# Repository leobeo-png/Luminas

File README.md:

# Luminas
Rhythm game controller development (Pro Micro). WIP <br>
[Video Demo](https://www.youtube.com/watch?v=vNHZUSEBsMY "Early Prototype")
[Video Demo](https://www.youtube.com/watch?v=JDYHQ-9xTno "Prototype Update")
---
## Description
 - Custom keyboard NKRO HID 
 - PCB size for 15.6" laptop
 - ToF sensors instead of IR for compactness
---
## Components Used:
 - Arduino Pro Micro
 - MPR121 Modules x3
 - VL53L0X ToF sensors x2 
 - TCA9548 I2C Multiplexer
 - Pull-up resistors
---
## Goals
 - Improve the design of the PCB 
 - Reaserch and design the casing
--- 
## What I Learnt so Far 
 - HID (descriptors, how NKRO works)
 - PCB schematic designing
 - Diving further into I2C

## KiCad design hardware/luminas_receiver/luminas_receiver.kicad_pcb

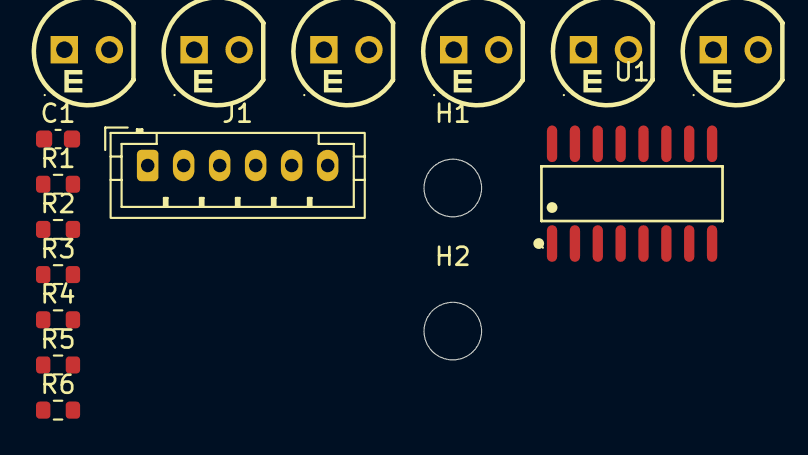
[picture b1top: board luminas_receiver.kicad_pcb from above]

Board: 2 copper layers, 17 parts (0 on the bottom side), 12 nets, no tracks yet.

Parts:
C1: 100nF; C_0603_1608Metric
H1, H2: MountingHole; MountingHole_3.2mm_M3
J1: Conn_01x06; JST_PH_B6B-PH-K_1x06_P2.00mm_Vertical
Q1, Q2, Q3, Q4, Q5, Q6: PT333-3B_C5134; SENSOR-TH_PT333-3B
R1, R2, R3, R4, R5, R6: 47k; R_0603_1608Metric
U1: 74LV4051D,118; SO-16_L9.9-W3.9-P1.27-LS6.0-BL

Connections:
+3V3: C1.1, J1.1, Q1.2 (C), Q2.2 (C), Q3.2 (C), Q4.2 (C), Q5.2 (C), Q6.2 (C), U1.16 (VCC)
/Y0: Q1.1 (E), R1.1, U1.13 (Y0)
/Y1: Q2.1 (E), R2.1, U1.14 (Y1)
/Y2: Q3.1 (E), R3.1, U1.15 (Y2)
/Y3: Q4.1 (E), R4.1, U1.12 (Y3)
/Y4: Q5.1 (E), R5.1, U1.1 (Y4)
/Y5: Q6.1 (E), R6.1, U1.5 (Y5)
AIR_OUT: J1.6, U1.3 (Z)
GND: C1.2, J1.2, R1.2, R2.2, R3.2, R4.2, R5.2, R6.2, U1.2 (Y6), U1.4 (Y7), U1.6 (~E), U1.7 (VEE), U1.8 (VSS)
IR_SEL0: J1.3, U1.11 (S0)
IR_SEL1: J1.4, U1.10 (S1)
IR_SEL2: J1.5, U1.9 (S2)

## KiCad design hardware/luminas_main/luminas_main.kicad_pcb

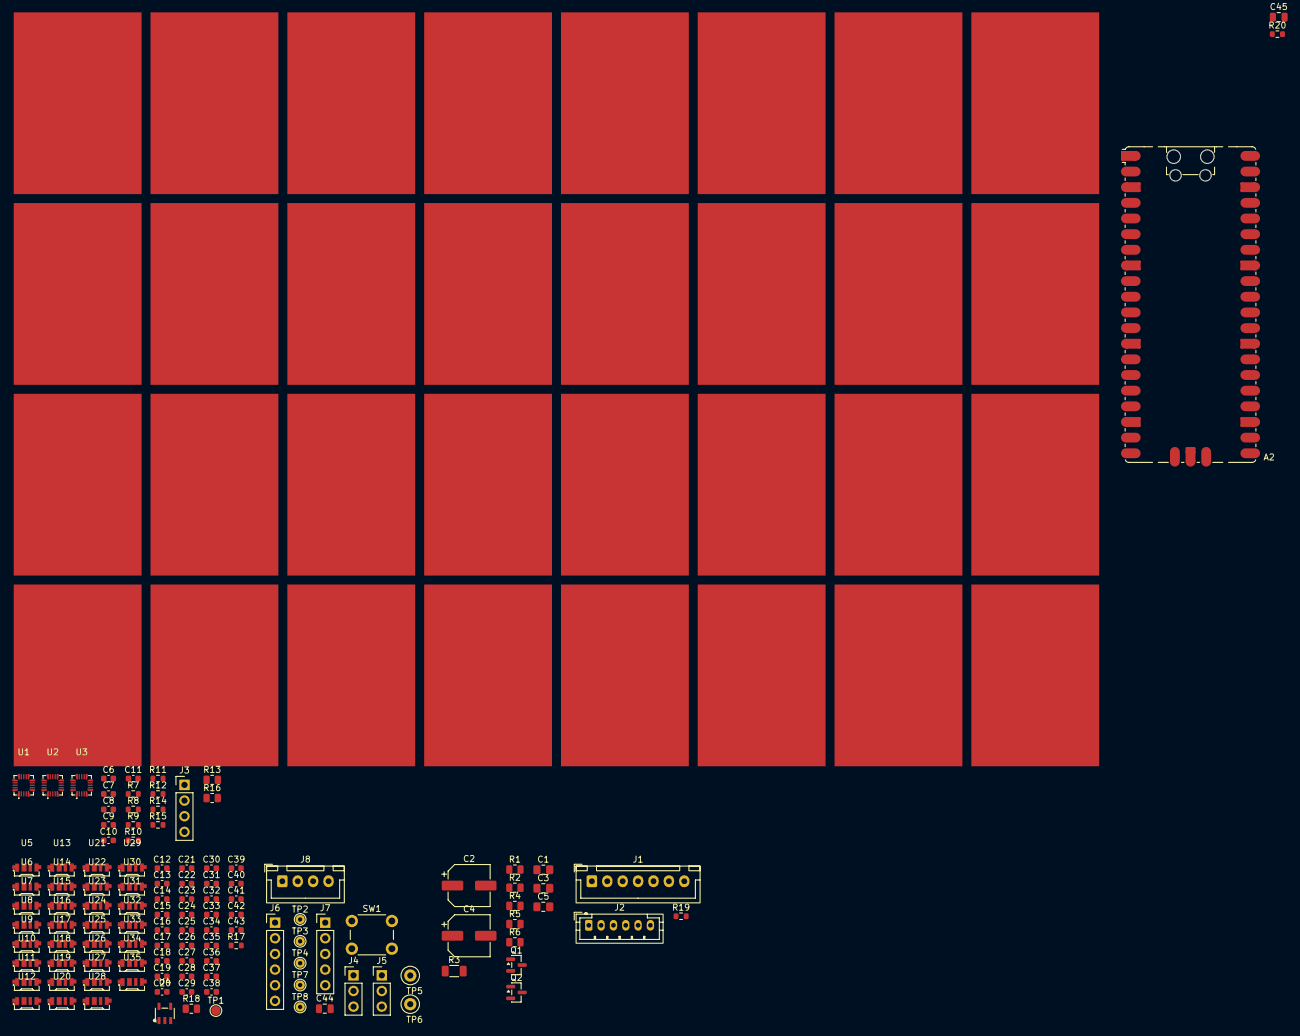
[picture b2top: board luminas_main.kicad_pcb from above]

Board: 2 copper layers, 152 parts (0 on the bottom side), 107 nets, no tracks yet.

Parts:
A2: RaspberryPi_Pico; RaspberryPi_Pico_SMD_HandSolder
C1: 47nF; C_0805_2012Metric_Pad1.18x1.45mm_HandSolder
C2: 100uF 16V; CP_Elec_6.3x7.7
C3: 10uF; C_0805_2012Metric_Pad1.18x1.45mm_HandSolder
C4: 100uF; CP_Elec_6.3x7.7
C5: 10nF; C_0805_2012Metric_Pad1.18x1.45mm_HandSolder
C6, C7, C8, C9, C10, C11, C12, C13, C14, C15, C16, C17, C18, C19, C20, C21, C22, C23, C24, C25, C26, C27, C28, C29, C30, C31, C32, C33, C34, C35, C36, C37, C38, C39, C40, C41, C42, C43: 100nF; C_0603_1608Metric
C44: 100nF; C_0805_2012Metric
C45: 1nF; C_0805_2012Metric
E1, E2, E3, E4, E5, E6, E7, E8, E9, E10, E11, E12, E13, E14, E15, E16, E17, E18, E19, E20, E21, E22, E23, E24, E25, E26, E27, E28, E29, E30, E31, E32: Touch_Pad
J1: IR conn; JST_XH_B7B-XH-A_1x07_P2.50mm_Vertical
J2: Air out conn; JST_PH_B6B-PH-K_1x06_P2.00mm_Vertical
J3: Spare I2C1; PinHeader_1x04_P2.54mm_Vertical
J4: SWD header; PinHeader_1x03_P2.54mm_Vertical
J5: UART header; PinHeader_1x03_P2.54mm_Vertical
J6: Logic-analyser header; PinHeader_1x06_P2.54mm_Vertical
J7: Spare Analog; PinHeader_1x05_P2.54mm_Vertical
J8: Conn_01x04; JST_XH_B4B-XH-A_1x04_P2.50mm_Vertical
Q1: AO3401A; SOT-23
Q2: 2N7002; SOT-23
R1, R4, R5, R6: 100kΩ; R_0805_2012Metric
R2: 47kΩ; R_0805_2012Metric
R3: 0Ω; R_1206_3216Metric
R7, R8: 2.2kΩ; R_0603_1608Metric
R9, R14, R15: 10kΩ; R_0603_1608Metric
R10, R11, R12: 75kΩ 1%; R_0603_1608Metric
R13, R16: 2.2kΩ; R_0805_2012Metric
R17: 33Ω; R_0603_1608Metric
R18: 0Ω; R_0805_2012Metric
R19: 100k; R_0603_1608Metric
R20: 0Ω; R_0603_1608Metric
SW1: RESET; SW_PUSH_6mm
TP1: LED_CHAIN_END; TestPoint_Pad_D1.5mm
TP2: +3V3; TestPoint_THTPad_D1.5mm_Drill0.7mm
TP3: 5V_SW; TestPoint_THTPad_D1.5mm_Drill0.7mm
TP4: VBUS; TestPoint_THTPad_D1.5mm_Drill0.7mm
TP5, TP6: GND; TestPoint_Loop_D2.50mm_Drill1.0mm
TP7: AIR_OUT; TestPoint_THTPad_D1.5mm_Drill0.7mm
TP8: IR_EN; TestPoint_THTPad_D1.5mm_Drill0.7mm
U1, U2, U3: MPR121QR2; QFN-20_L3.0-W3.0-P0.40-BL
U4: 74AHCT1G125GV; SOT-23-5_L3.0-W1.7-P0.95-LS2.8-BL
U5, U6, U7, U8, U9, U10, U11, U12, U13, U14, U15, U16, U17, U18, U19, U20, U21, U22, U23, U24, U25, U26, U27, U28, U29, U30, U31, U32, U33, U34, U35: WS2812B-4020-V6; LED-SMD_4P-L4.0-W1.6-L

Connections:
5V_SW: C1.1, C2.1, C3.2, C4.1, C12.1, C13.1, C14.1, C15.1, C16.1, C17.1, C18.1, C19.1, C20.1, C21.1, C22.1, C23.1, C24.1, C25.1, C26.1, C27.1, C28.1, C29.1, C30.1, C31.1, C32.1, C33.1, C34.1, C35.1, C36.1, C37.1, C38.1, C39.1, C40.1, C41.1, C42.1, C43.1, J1.1, Q1.3 (D), R3.1, R5.1, TP3.1 (1_1), U4.5 (VCC), U5.2 (VDD), U6.2 (VDD), U7.2 (VDD), U8.2 (VDD), U9.2 (VDD), U10.2 (VDD), U11.2 (VDD), U12.2 (VDD), U13.2 (VDD), U14.2 (VDD), U15.2 (VDD), U16.2 (VDD), U17.2 (VDD), U18.2 (VDD), U19.2 (VDD), U20.2 (VDD), U21.2 (VDD), U22.2 (VDD), U23.2 (VDD), U24.2 (VDD), U25.2 (VDD), U26.2 (VDD), U27.2 (VDD), U28.2 (VDD), U29.2 (VDD), U30.2 (VDD), U31.2 (VDD), U32.2 (VDD), U33.2 (VDD), U34.2 (VDD), U35.2 (VDD)
+3V3: A2.36 (3V3), C6.1, C9.1, C11.1, J1.3, J2.1, J3.2, J7.5, R7.1, R8.1, R9.1, R13.2, R14.1, R15.1, R16.2, TP2.1 (1_1), U1.20 (VDD), U2.4 (ADDR), U2.20 (VDD), U3.20 (VDD)
/Touch/ZONE00: E1.1, U1.8 (ELE0)
/Touch/ZONE01: E2.1, U1.9 (ELE1)
/Touch/ZONE02: E3.1, U1.10 (ELE2)
/Touch/ZONE03: E4.1, U1.11 (ELE3)
/Touch/ZONE04: E5.1, U1.12 (ELE4)
/Touch/ZONE05: E6.1, U1.13 (ELE5)
/Touch/ZONE06: E7.1, U1.14 (ELE6)
/Touch/ZONE07: E8.1, U1.15 (ELE7)
/Touch/ZONE08: E9.1, U1.16 (ELE8)
/Touch/ZONE09: E10.1, U1.17 (ELE9)
/Touch/ZONE10: E11.1, U1.18 (ELE10)
/Touch/ZONE11: E12.1, U1.19 (ELE11)
/Touch/ZONE12: E13.1, U2.8 (ELE0)
/Touch/ZONE13: E14.1, U2.9 (ELE1)
/Touch/ZONE14: E15.1, U2.10 (ELE2)
/Touch/ZONE15: E16.1, U2.11 (ELE3)
/Touch/ZONE16: E17.1, U2.12 (ELE4)
/Touch/ZONE17: E18.1, U2.13 (ELE5)
/Touch/ZONE18: E19.1, U2.14 (ELE6)
/Touch/ZONE19: E20.1, U2.15 (ELE7)
/Touch/ZONE20: E21.1, U2.16 (ELE8)
/Touch/ZONE21: E22.1, U2.17 (ELE9)
/Touch/ZONE22: E23.1, U2.18 (ELE10)
/Touch/ZONE23: E24.1, U2.19 (ELE11)
/Touch/ZONE24: E25.1, U3.8 (ELE0)
/Touch/ZONE25: E26.1, U3.9 (ELE1)
/Touch/ZONE26: E27.1, U3.10 (ELE2)
/Touch/ZONE27: E28.1, U3.11 (ELE3)
/Touch/ZONE28: E29.1, U3.12 (ELE4)
/Touch/ZONE29: E30.1, U3.13 (ELE5)
/Touch/ZONE30: E31.1, U3.14 (ELE6)
/Touch/ZONE31: E32.1, U3.15 (ELE7)
AIR_OUT: C45.1, J2.6, R20.2, TP7.1 (1_1)
DBG0: A2.25 (GPIO19), J6.4
DBG1: A2.26 (GPIO20), J6.5
DBG2: A2.27 (GPIO21), J6.6
GND: A2.3 (GND), A2.8 (GND), A2.13 (GND), A2.18 (GND), A2.23 (GND), A2.28 (GND), A2.33 (AGND), A2.38 (GND), A2.D2 (GND), C2.2, C3.1, C4.2, C5.1, C6.2, C7.2, C8.2, C9.2, C10.2, C11.2, C12.2, C13.2, C14.2, C15.2, C16.2, C17.2, C18.2, C19.2, C20.2, C21.2, C22.2, C23.2, C24.2, C25.2, C26.2, C27.2, C28.2, C29.2, C30.2, C31.2, C32.2, C33.2, C34.2, C35.2, C36.2, C37.2, C38.2, C39.2, C40.2, C41.2, C42.2, C43.2, C44.2, C45.2, J1.2, J2.2, J3.1, J4.2, J5.1, J6.1, J7.1, J8.1, Q2.2 (S), R4.1, R6.2, R10.2, R11.2, R12.2, R19.2, SW1.2, TP5.1 (1_1), TP6.1 (1_1), U1.4 (ADDR), U1.6 (VSS), U2.6 (VSS), U3.6 (VSS), U4.1 (~OE), U4.3 (GND), U5.4 (VSS), U6.4 (VSS), U7.4 (VSS), U8.4 (VSS), U9.4 (VSS), U10.4 (VSS), U11.4 (VSS), U12.4 (VSS), U13.4 (VSS), U14.4 (VSS), U15.4 (VSS), U16.4 (VSS), U17.4 (VSS), U18.4 (VSS), U19.4 (VSS), U20.4 (VSS), U21.4 (VSS), U22.4 (VSS), U23.4 (VSS), U24.4 (VSS), U25.4 (VSS), U26.4 (VSS), U27.4 (VSS), U28.4 (VSS), U29.4 (VSS), U30.4 (VSS), U31.4 (VSS), U32.4 (VSS), U33.4 (VSS), U34.4 (VSS), U35.4 (VSS)
I2C0_SCL: A2.7 (GPIO5), J6.3, R8.2, U1.2 (SCL), U2.2 (SCL), U3.2 (SCL)
I2C0_SDA: A2.6 (GPIO4), J6.2, R7.2, U1.3 (SDA), U2.3 (SDA), U3.3 (SDA), U3.4 (ADDR)
I2C1_SCL: A2.5 (GPIO3), J3.4, R16.1
I2C1_SDA: A2.4 (GPIO2), J3.3, R13.1
IR_EN: A2.17 (GPIO13), J1.7, R19.1, TP8.1 (1_1)
IR_SEL0: A2.14 (GPIO10), J1.4, J2.3
IR_SEL1: A2.15 (GPIO11), J1.5, J2.4
IR_SEL2: A2.16 (GPIO12), J1.6, J2.5
LED_5V_EN: A2.19 (GPIO14), Q2.1 (G), R4.2
LED_DATA: A2.20 (GPIO15), R18.2, U4.2 (A)
unnamed: A2.31 (GPIO26_ADC0), R20.1
unnamed: C1.2, Q1.1 (G), R1.1, R2.2
unnamed: Q2.3 (D), R2.1
unnamed: R10.1, U1.7 (REXT)
unnamed: C7.1, U1.5 (VREG)
unnamed: R11.1, U2.7 (REXT)
unnamed: C8.1, U2.5 (VREG)
unnamed: R12.1, U3.7 (REXT)
unnamed: C10.1, U3.5 (VREG)
unnamed: R17.2, U4.4 (Y)
unnamed: R17.1, R18.1, U5.1 (DIN)
unnamed: U5.3 (DOUT), U6.1 (DIN)
unnamed: U6.3 (DOUT), U7.1 (DIN)
unnamed: U7.3 (DOUT), U8.1 (DIN)
unnamed: U8.3 (DOUT), U9.1 (DIN)
unnamed: U9.3 (DOUT), U10.1 (DIN)
unnamed: U10.3 (DOUT), U11.1 (DIN)
unnamed: U11.3 (DOUT), U12.1 (DIN)
unnamed: U12.3 (DOUT), U13.1 (DIN)
unnamed: U13.3 (DOUT), U14.1 (DIN)
unnamed: U14.3 (DOUT), U15.1 (DIN)
unnamed: U15.3 (DOUT), U16.1 (DIN)
unnamed: U16.3 (DOUT), U17.1 (DIN)
unnamed: U17.3 (DOUT), U18.1 (DIN)
unnamed: U18.3 (DOUT), U19.1 (DIN)
unnamed: U19.3 (DOUT), U20.1 (DIN)
unnamed: U20.3 (DOUT), U21.1 (DIN)
unnamed: U21.3 (DOUT), U22.1 (DIN)
unnamed: U22.3 (DOUT), U23.1 (DIN)
unnamed: U23.3 (DOUT), U24.1 (DIN)
unnamed: U24.3 (DOUT), U25.1 (DIN)
unnamed: U25.3 (DOUT), U26.1 (DIN)
unnamed: U26.3 (DOUT), U27.1 (DIN)
unnamed: U27.3 (DOUT), U28.1 (DIN)
unnamed: U28.3 (DOUT), U29.1 (DIN)
unnamed: U29.3 (DOUT), U30.1 (DIN)
unnamed: U30.3 (DOUT), U31.1 (DIN)
unnamed: U31.3 (DOUT), U32.1 (DIN)
unnamed: U32.3 (DOUT), U33.1 (DIN)
unnamed: U33.3 (DOUT), U34.1 (DIN)
unnamed: U34.3 (DOUT), U35.1 (DIN)
unnamed: TP1.1 (1_1), U35.3 (DOUT)
RUN: A2.30 (RUN), C44.1, SW1.1
SERVICE: A2.22 (GPIO17), J8.3
SPARE_GP9: A2.12 (GPIO9), J7.2
SPARE_GP22: A2.29 (GPIO22), J7.3
SPARE_GP28: A2.34 (GPIO28_ADC2), J7.4
START: A2.24 (GPIO18), J8.4
SWCLK: A2.D1 (SWCLK), J4.1
SWDIO: A2.D3 (SWDIO), J4.3
TEST: A2.21 (GPIO16), J8.2
TOUCH_IRQ0: A2.9 (GPIO6), R9.2, U1.1 (~IRQ)
TOUCH_IRQ1: A2.10 (GPIO7), R14.2, U2.1 (~IRQ)
TOUCH_IRQ2: A2.11 (GPIO8), R15.2, U3.1 (~IRQ)
UART_RX: A2.2 (GPIO1), J5.3
UART_TX: A2.1 (GPIO0), J5.2
V5SW_SENSE: A2.32 (GPIO27_ADC1), C5.2, R5.2, R6.1
VBUS: A2.40 (VBUS), Q1.2 (S), R1.2, R3.2, TP4.1 (1_1)

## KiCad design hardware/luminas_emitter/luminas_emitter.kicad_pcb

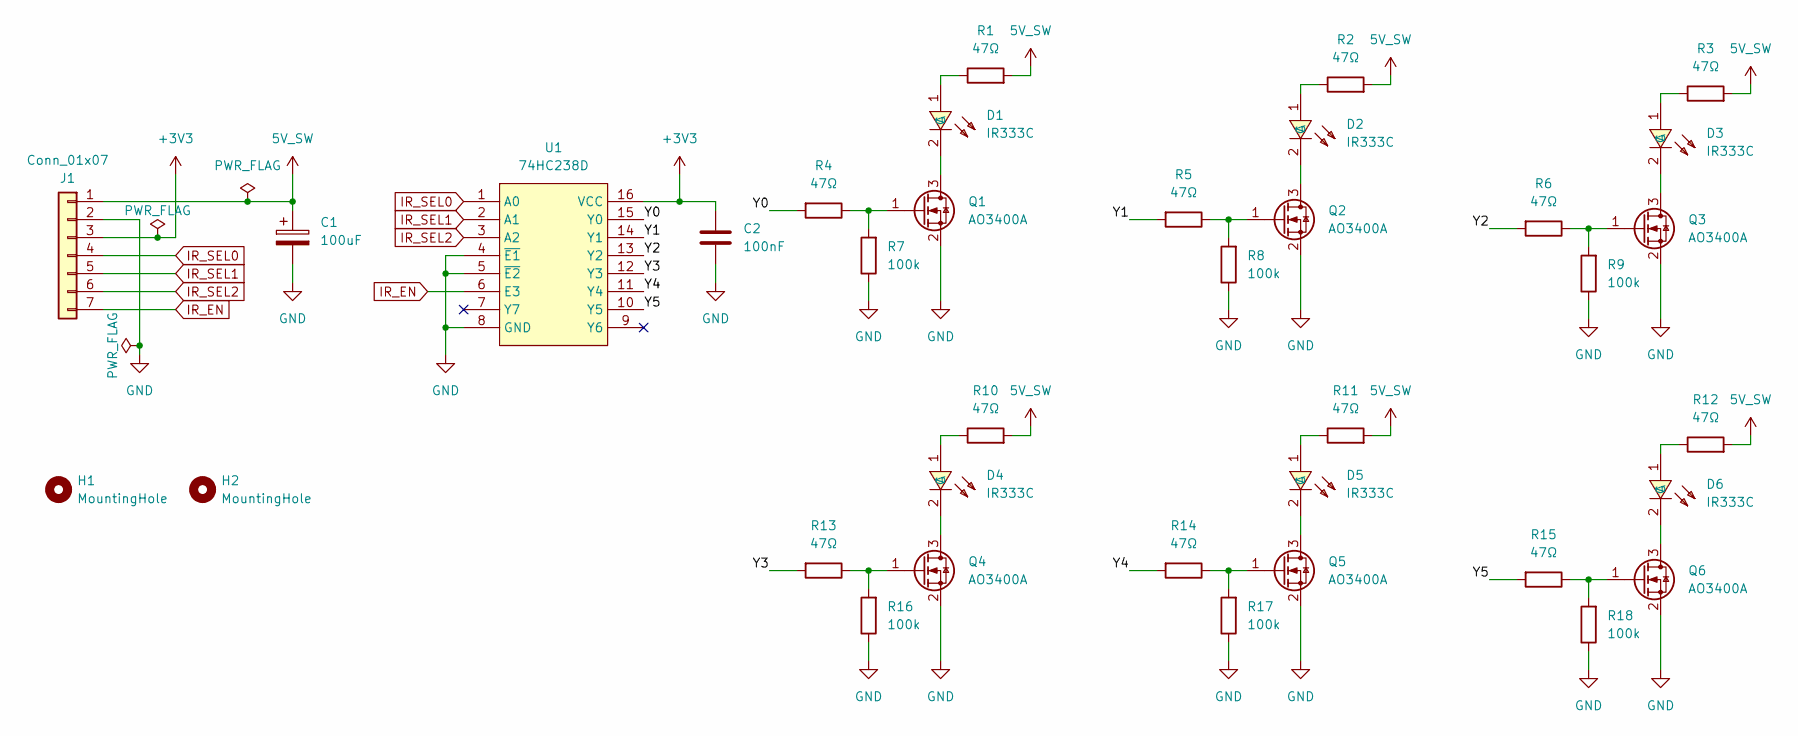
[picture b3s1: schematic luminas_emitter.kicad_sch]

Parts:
C1: 100uF; CP_Elec_6.3x7.7; LCSC Part C72476
C2: 100nF; C_0603_1608Metric; LCSC Part C14663
D1, D2, D3, D4, D5, D6: IR333C; LED-TH_BD5.0-P2.54-FD; MPN IR333C; LCSC Part C5200795
H1, H2: MountingHole; MountingHole_3.2mm_M3
J1: Conn_01x07; JST_XH_B7B-XH-A_1x07_P2.50mm_Vertical
Q1, Q2, Q3, Q4, Q5, Q6: AO3400A; SOT-23; LCSC Part C20917
R1, R2, R3, R4, R5, R6, R10, R11, R12, R13, R14, R15: 47Ω; R_0805_2012Metric; LCSC Part C17714
R7, R8, R9, R16, R17, R18: 100k; R_0603_1608Metric; LCSC Part C25803
U1: 74HC238D; SOIC-16_L9.9-W3.9-P1.27-LS6.0-BL; MPN 74HC238D,653; LCSC Part C5620

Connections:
5V_SW: C1.1, J1.1, R1.2, R2.2, R3.2, R10.2, R11.2, R12.2
+3V3: C2.1, J1.3, U1.16 (VCC)
/Y0: R4.2, U1.15 (Y0)
/Y1: R5.2, U1.14 (Y1)
/Y2: R6.2, U1.13 (Y2)
/Y3: R13.2, U1.12 (Y3)
/Y4: R14.2, U1.11 (Y4)
/Y5: R15.2, U1.10 (Y5)
GND: C1.2, C2.2, J1.2, Q1.2 (S), Q2.2 (S), Q3.2 (S), Q4.2 (S), Q5.2 (S), Q6.2 (S), R7.1, R8.1, R9.1, R16.1, R17.1, R18.1, U1.4 (~E1), U1.5 (~E2), U1.8 (GND)
IR_EN: J1.7, U1.6 (E3)
IR_SEL0: J1.4, U1.1 (A0)
IR_SEL1: J1.5, U1.2 (A1)
IR_SEL2: J1.6, U1.3 (A2)
unnamed: D1.1 (A), R1.1
unnamed: D1.2 (C), Q1.3 (D)
unnamed: D2.1 (A), R2.1
unnamed: D2.2 (C), Q2.3 (D)
unnamed: D3.1 (A), R3.1
unnamed: D3.2 (C), Q3.3 (D)
unnamed: D4.1 (A), R10.1
unnamed: D4.2 (C), Q4.3 (D)
unnamed: D5.1 (A), R11.1
unnamed: D5.2 (C), Q5.3 (D)
unnamed: D6.1 (A), R12.1
unnamed: D6.2 (C), Q6.3 (D)
unnamed: Q1.1 (G), R4.1, R7.2
unnamed: Q2.1 (G), R5.1, R8.2
unnamed: Q3.1 (G), R6.1, R9.2
unnamed: Q4.1 (G), R13.1, R16.2
unnamed: Q5.1 (G), R14.1, R17.2
unnamed: Q6.1 (G), R15.1, R18.2

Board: 2 copper layers, 36 parts (0 on the bottom side), 31 nets, no tracks yet.

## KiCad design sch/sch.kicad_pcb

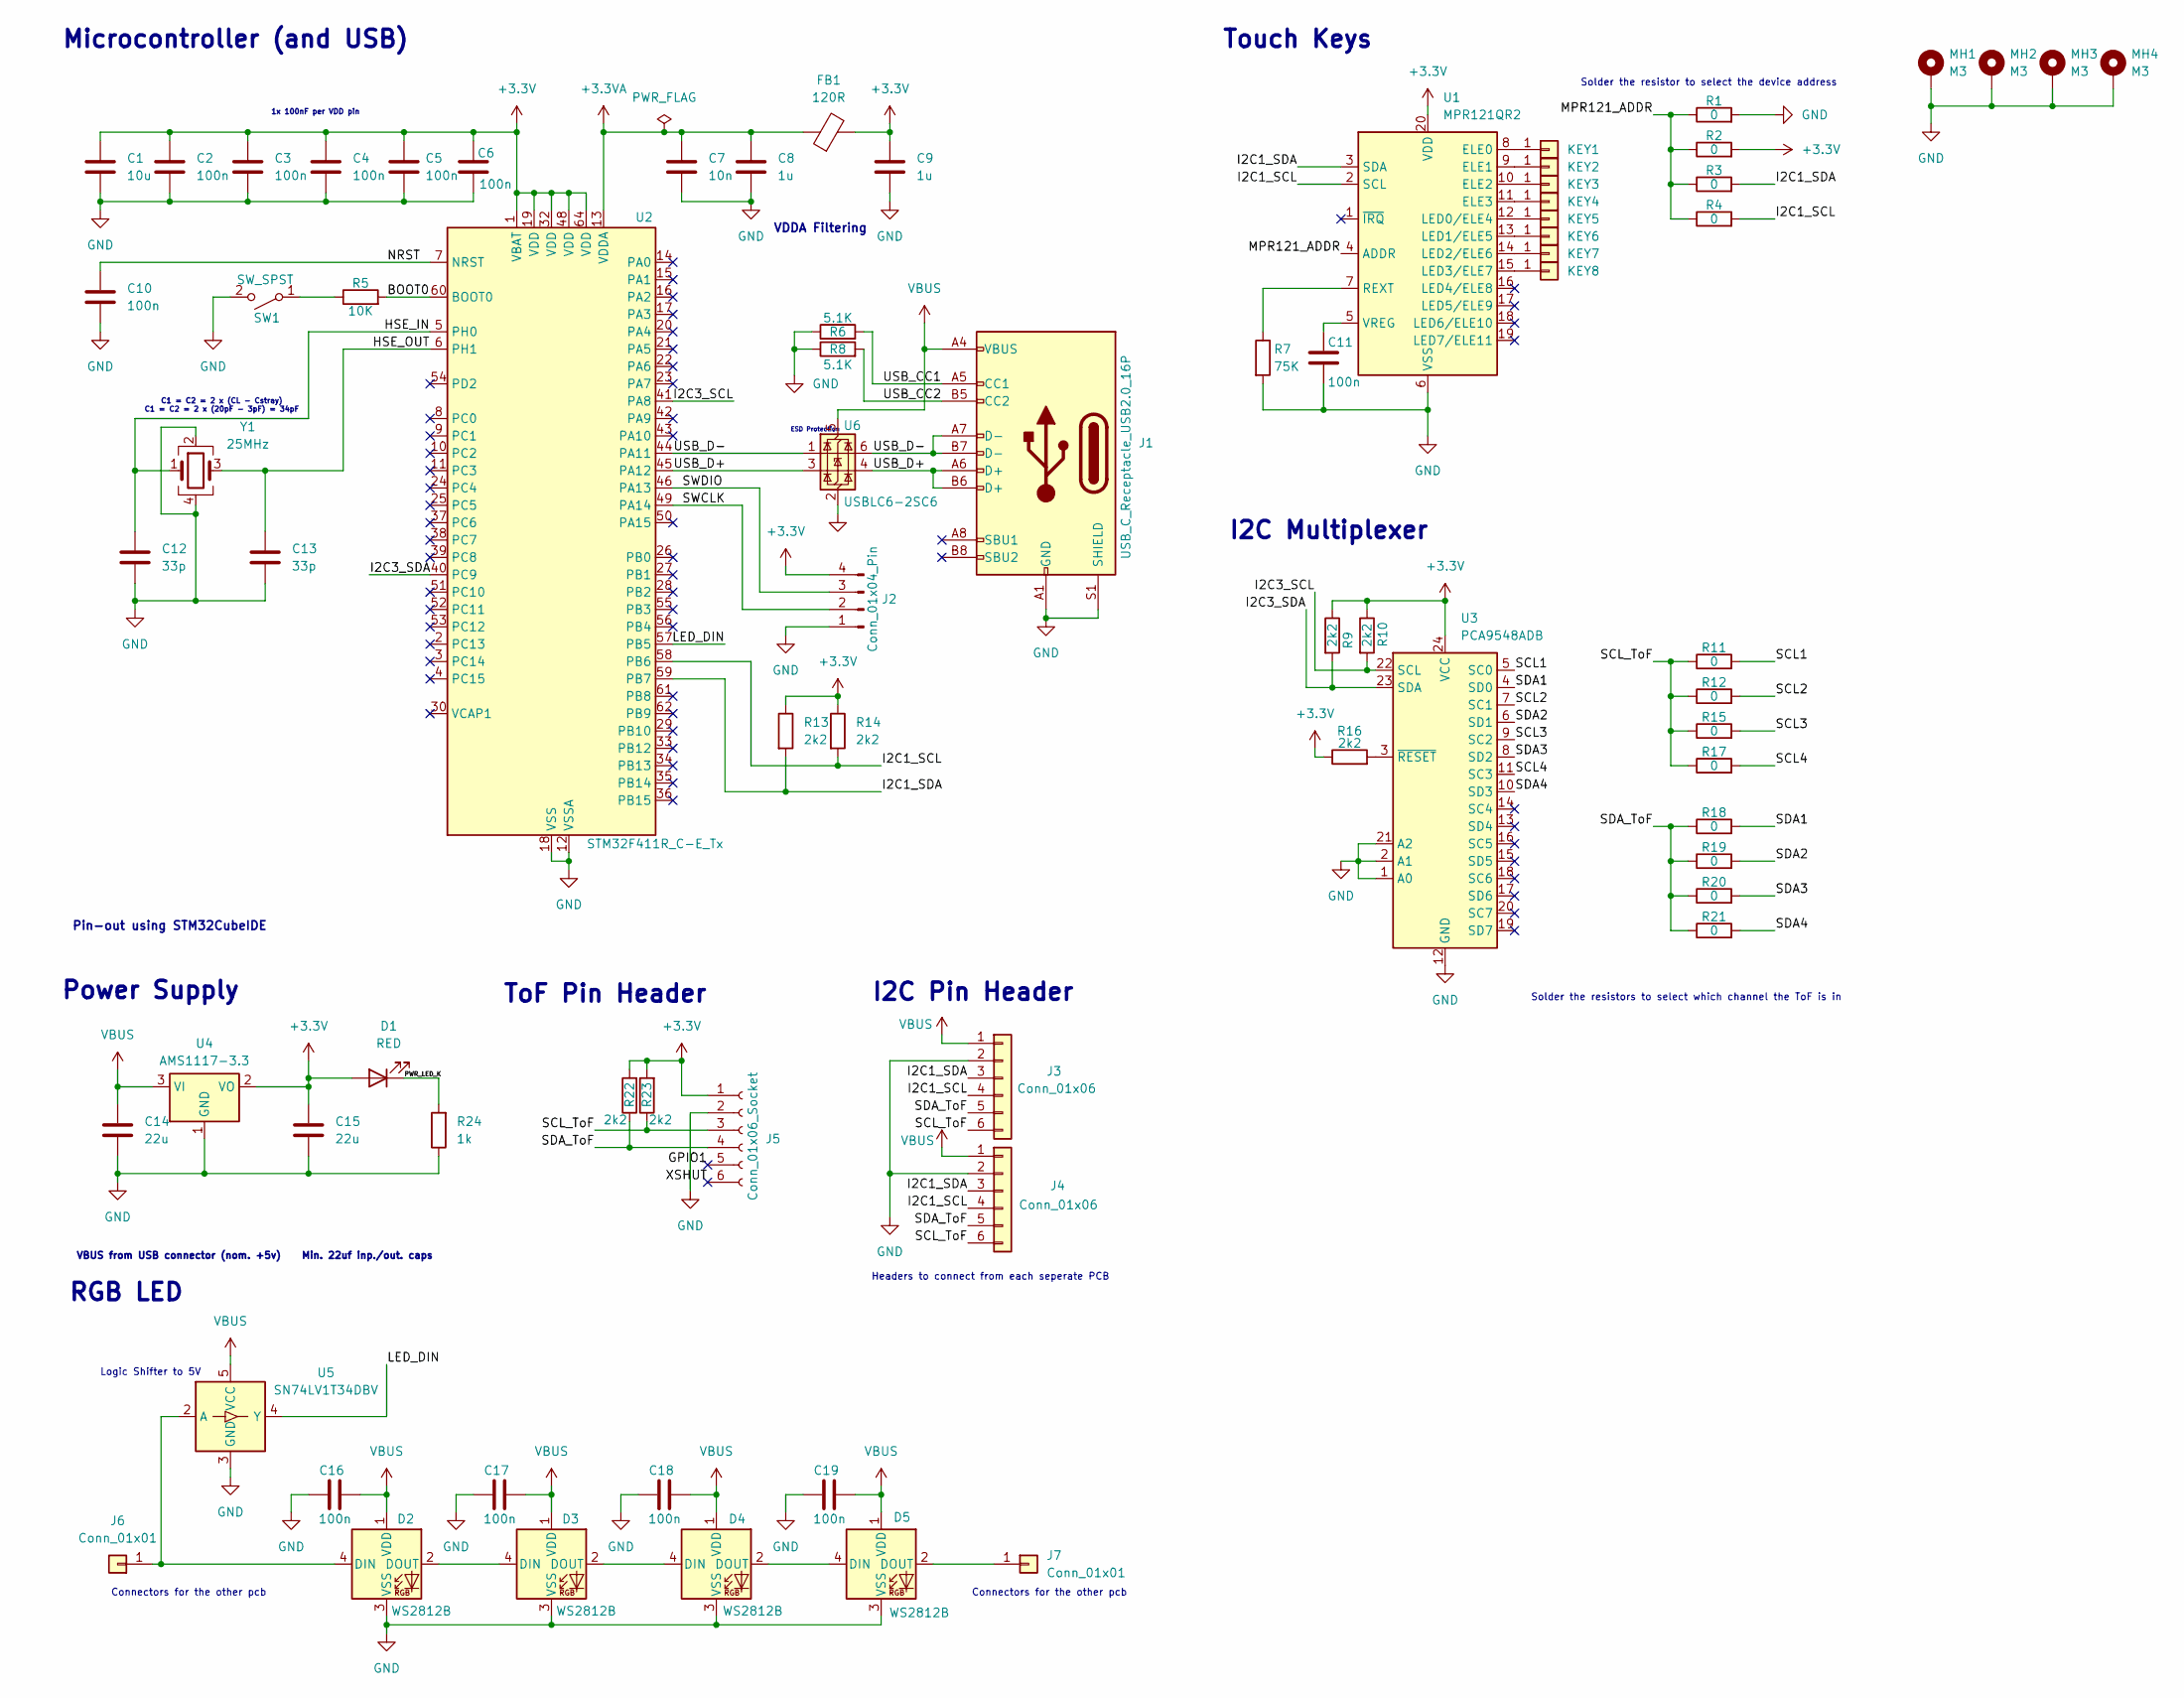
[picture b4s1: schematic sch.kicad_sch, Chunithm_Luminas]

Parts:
C1: 10u; C_0603_1608Metric_Pad1.08x0.95mm_HandSolder
C2, C3, C4, C5, C6, C10, C11, C16, C17, C18, C19: 100n; C_0603_1608Metric_Pad1.08x0.95mm_HandSolder
C7: 10n; C_0603_1608Metric_Pad1.08x0.95mm_HandSolder
C8, C9: 1u; C_0603_1608Metric_Pad1.08x0.95mm_HandSolder
C12, C13: 33p; C_0603_1608Metric_Pad1.08x0.95mm_HandSolder
C14, C15: 22u; C_0805_2012Metric
D1: RED; LED_0201_0603Metric
D2, D3, D4, D5: WS2812B; LED_WS2812B_PLCC4_5.0x5.0mm_P3.2mm
FB1: 120R; L_0603_1608Metric
J1: USB_C_Receptacle_USB2.0_16P; USB_C_Receptacle_GCT_USB4105-xx-A_16P_TopMnt_Horizontal
J2: Conn_01x04_Pin; PinHeader_1x04_P2.54mm_Vertical
J3, J4: Conn_01x06; Conn_Solder_I2C
J5: Conn_01x06_Socket; PinHeader_1x06_P2.54mm_Vertical
J6, J7: Conn_01x01; Solder_3P
KEY1, KEY2, KEY3, KEY4, KEY5, KEY6, KEY7, KEY8: Conn_01x01; ChuKey
MH1, MH2, MH3, MH4: M3; MountingHole_3.2mm_M3_Pad_Via
R1, R2, R3, R4, R11, R12, R15, R17, R18, R19, R20, R21: 0; R_0603_1608Metric_Pad0.98x0.95mm_HandSolder
R5: 10K; R_0603_1608Metric_Pad0.98x0.95mm_HandSolder
R6, R8: 5.1K; R_0603_1608Metric_Pad0.98x0.95mm_HandSolder
R7: 75K; R_0603_1608Metric_Pad0.98x0.95mm_HandSolder
R9, R10, R13, R14, R16, R22, R23: 2k2; R_0603_1608Metric_Pad0.98x0.95mm_HandSolder
R24: 1k; R_0603_1608Metric_Pad0.98x0.95mm_HandSolder
SW1: SW_SPST; SW_SPST_TS-1088-xR025
U1: MPR121QR2; UQFN-20_3x3mm_P0.4mm
U2: STM32F411R_C-E_Tx; LQFP-64_10x10mm_P0.5mm
U3: PCA9548ADB; TSSOP-24_4.4x7.8mm_P0.65mm
U4: AMS1117-3.3; SOT-223-3_TabPin2
U5: SN74LV1T34DBV; SOT-23-5
U6: USBLC6-2SC6; SOT-23-6
Y1: 25MHz; Crystal_SMD_3225-4Pin_3.2x2.5mm_HandSoldering

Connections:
+3.3V: C1.1, C2.1, C3.1, C4.1, C5.1, C6.1, C9.1, C15.1, D1.2 (A), FB1.2, J2.4, J5.1, R2.2, R9.1, R10.1, R13.1, R14.1, R16.1, R22.2, R23.2, U1.20 (VDD), U2.1 (VBAT), U2.19 (VDD), U2.32 (VDD), U2.48 (VDD), U2.64 (VDD), U3.24 (VCC), U4.2 (VO)
+3.3VA: C7.1, C8.1, FB1.1, U2.13 (VDDA)
/BOOT0: R5.2, U2.60 (BOOT0)
/GPIO1: J5.5
/HSE_IN: C12.1, U2.5 (PH0), Y1.1
/HSE_OUT: C13.1, U2.6 (PH1), Y1.3
/I2C1_SCL: J3.4, J4.4, R4.2, R14.2, U1.2 (SCL), U2.58 (PB6)
/I2C1_SDA: J3.3, J4.3, R3.2, R13.2, U1.3 (SDA), U2.59 (PB7)
/I2C3_SCL: R10.2, U2.41 (PA8), U3.22 (SCL)
/I2C3_SDA: R9.2, U2.40 (PC9), U3.23 (SDA)
/LED_DIN: U2.57 (PB5), U5.4 (Y)
/MPR121_ADDR: R1.1, R2.1, R3.1, R4.1, U1.4 (ADDR)
/NRST: C10.1, U2.7 (NRST)
/PWR_LED_K: D1.1 (K), R24.2
/SCL1: R11.2, U3.5 (SC0)
/SCL2: R12.2, U3.7 (SC1)
/SCL3: R15.2, U3.9 (SC2)
/SCL4: R17.2, U3.11 (SC3)
/SCL_ToF: J3.6, J4.6, J5.3, R11.1, R12.1, R15.1, R17.1, R23.1
/SDA1: R18.2, U3.4 (SD0)
/SDA2: R19.2, U3.6 (SD1)
/SDA3: R20.2, U3.8 (SD2)
/SDA4: R21.2, U3.10 (SD3)
/SDA_ToF: J3.5, J4.5, J5.4, R18.1, R19.1, R20.1, R21.1, R22.1
/SWCLK: J2.2, U2.49 (PA14)
/SWDIO: J2.3, U2.46 (PA13)
/USB_CC1: J1.A5 (CC1), R6.2
/USB_CC2: J1.B5 (CC2), R8.2
/USB_D+: J1.A6 (D+), J1.B6 (D+), U2.45 (PA12), U6.3 (I/O2), U6.4 (I/O2)
/USB_D-: J1.A7 (D-), J1.B7 (D-), U2.44 (PA11), U6.1 (I/O1), U6.6 (I/O1)
/XSHUT: J5.6
GND: C1.2, C2.2, C3.2, C4.2, C5.2, C6.2, C7.2, C8.2, C9.2, C10.2, C11.2, C12.2, C13.2, C14.2, C15.2, C16.1, C17.1, C18.1, C19.1, D2.3 (VSS), D3.3 (VSS), D4.3 (VSS), D5.3 (VSS), J1.A1 (GND), J1.A12 (GND), J1.B1 (GND), J1.B12 (GND), J1.S1 (SHIELD), J2.1, J3.2, J4.2, J5.2, MH1.1, MH2.1, MH3.1, MH4.1, R1.2, R6.1, R7.2, R8.1, R24.1, SW1.2 (B), U1.6 (VSS), U2.12 (VSSA), U2.18 (VSS), U2.31 (VSS), U2.47 (VSS), U2.63 (VSS), U3.1 (A0), U3.2 (A1), U3.12 (GND), U3.21 (A2), U4.1 (GND), U5.3 (GND), U6.2 (GND), Y1.2, Y1.4
unnamed: D2.4 (DIN), J6.1, U5.2 (A)
unnamed: D2.2 (DOUT), D3.4 (DIN)
unnamed: D3.2 (DOUT), D4.4 (DIN)
unnamed: D4.2 (DOUT), D5.4 (DIN)
unnamed: D5.2 (DOUT), J7.1
unnamed: KEY1.1, U1.8 (ELE0)
unnamed: KEY2.1, U1.9 (ELE1)
unnamed: KEY3.1, U1.10 (ELE2)
unnamed: KEY4.1, U1.11 (ELE3)
unnamed: KEY5.1, U1.12 (LED0/ELE4)
unnamed: KEY6.1, U1.13 (LED1/ELE5)
unnamed: KEY7.1, U1.14 (LED2/ELE6)
unnamed: KEY8.1, U1.15 (LED3/ELE7)
unnamed: R5.1, SW1.1 (A)
unnamed: R7.1, U1.7 (REXT)
unnamed: C11.1, U1.5 (VREG)
unnamed: R16.2, U3.3 (~RESET)
VBUS: C14.1, C16.2, C17.2, C18.2, C19.2, D2.1 (VDD), D3.1 (VDD), D4.1 (VDD), D5.1 (VDD), J1.A4 (VBUS), J1.A9 (VBUS), J1.B4 (VBUS), J1.B9 (VBUS), J3.1, J4.1, U4.3 (VI), U5.5 (VCC), U6.5 (VBUS)

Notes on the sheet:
Connectors for the other pcb
I2C Multiplexer
Solder the resistors to select which channel the ToF is in
VBUS from USB connector (nom. +5v) Min. 22uf inp./out. caps
Headers to connect from each seperate PCB
Microcontroller (and USB)
ESD Protection
VDDA Filtering
RGB LED
1x 100nF per VDD pin
I2C Pin Header
Solder the resistor to select the device address
Power Supply
Logic Shifter to 5V
Pin-out using STM32CubeIDE
Touch Keys
ToF Pin Header
C1 = C2 = 2 x (CL - Cstray) C1 = C2 = 2 x (20pF - 3pF) = 34pF

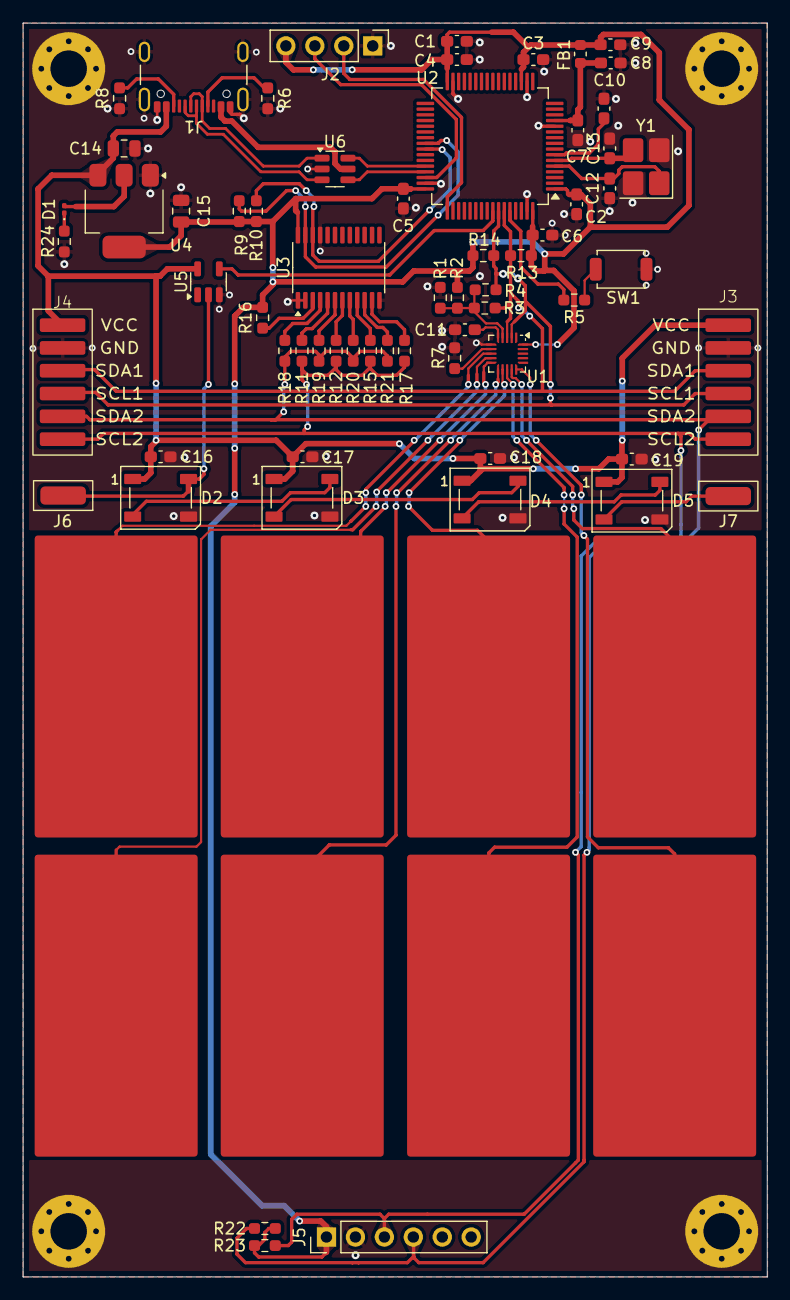
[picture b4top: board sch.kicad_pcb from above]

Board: 2 copper layers, 65.3 x 110.0 mm, 76 parts (0 on the bottom side), 48 nets.

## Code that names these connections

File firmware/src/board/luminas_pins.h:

/**
 * @file    luminas_pins.h
 * @brief   Luminas main board pin map (Architecture v0.4, section 3).
 *
 * @layer   board (no code, constants only; host-compilable)
 * @traces  SR-I-08, SR-R-07
 *
 * Module: Raspberry Pi Pico-compatible USB-C clone (D4).
 * GP23, GP24 and GP29 are module-internal and must not be used.
 */
#ifndef LUMINAS_PINS_H
#define LUMINAS_PINS_H

/* Debug UART (UART0) */
#define PIN_UART_TX         (0U)
#define PIN_UART_RX         (1U)

/* I2C1: spare header (ToF experiment) */
#define PIN_I2C1_SDA        (2U)
#define PIN_I2C1_SCL        (3U)

/* I2C0: MPR121 x3 (0x5A, 0x5B, 0x5C) */
#define PIN_I2C0_SDA        (4U)
#define PIN_I2C0_SCL        (5U)

/* MPR121 IRQ lines: open-drain, active low, 10 kOhm external pull-up */
#define PIN_TOUCH_IRQ0      (6U)
#define PIN_TOUCH_IRQ1      (7U)
#define PIN_TOUCH_IRQ2      (8U)

/* IR air towers (Appendix A) */
#define PIN_IR_SEL0         (10U)
#define PIN_IR_SEL1         (11U)
#define PIN_IR_SEL2         (12U)
#define PIN_IR_EN           (13U)   /* 100 kOhm external pull-down (R25)   */

/* Power */
#define PIN_LED_5V_EN       (14U)   /* D12 Q2 gate, 100 kOhm pull-down (R3) */

/* WS2812B data, PIO0 SM0, via 74AHCT1G125 */
#define PIN_LED_DATA        (15U)

/* Debug markers for latency measurement */
#define PIN_DBG0            (19U)
#define PIN_DBG1            (20U)
#define PIN_DBG2            (21U)

/* Module onboard LED */
#define PIN_STATUS_LED      (25U)

/* ADC */
#define PIN_AIR_OUT         (26U)   /* ADC0 */
#define PIN_V5SW_SENSE      (27U)   /* ADC1, optional divider */
#define ADC_CH_AIR_OUT      (0U)
#define ADC_CH_V5SW_SENSE   (1U)

/* Spare, broken out to pads: GP9, GP16, GP17, GP18, GP22, GP28 (ADC2).
 * No operator buttons: Test/Service/Coin stay on the PC keyboard (D13). */

/* I2C addresses (ADDR straps) */
#define MPR121_ADDR_0       (0x5AU)
#define MPR121_ADDR_1       (0x5BU)
#define MPR121_ADDR_2       (0x5CU)

#endif /* LUMINAS_PINS_H */

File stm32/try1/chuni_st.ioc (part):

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Mcu.Name=STM32F411C(C-E)Ux
Mcu.Package=UFQFPN48
Mcu.UserName=STM32F411CEUx
PA11.Mode=Device_Only
PA11.Signal=USB_OTG_FS_DM
PA12.Mode=Device_Only
PA12.Signal=USB_OTG_FS_DP
PA13.Mode=Serial_Wire
PA13.Signal=SYS_JTMS-SWDIO
PA14.Mode=Serial_Wire
PA14.Signal=SYS_JTCK-SWCLK
PB10.Mode=I2C
PB10.Signal=I2C2_SCL
PB3.Mode=I2C
PB3.Signal=I2C2_SDA
PB6.Mode=I2C
PB6.Signal=I2C1_SCL
PB7.Mode=I2C
PB7.Signal=I2C1_SDA
PC13-ANTI_TAMP.Signal=GPIO_Output
PH0\ -\ OSC_IN.Mode=HSE-External-Oscillator
PH0\ -\ OSC_IN.Signal=RCC_OSC_IN
PH1\ -\ OSC_OUT.Mode=HSE-External-Oscillator
PH1\ -\ OSC_OUT.Signal=RCC_OSC_OUT
RCC.HSE_VALUE=25000000
RCC.SYSCLKFreq_VALUE=96000000
RCC.SYSCLKSource=RCC_SYSCLKSOURCE_PLLCLK
board=custom

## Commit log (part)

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2024-11-06 First Itteration
    This version includes working NKRO and ToF. Although it might
    occasionally crash, probably because of memory? But i still don't know.
2024-11-06 Update README.md
    Updated it to its current state
2024-11-11 Fixed air keys
2025-04-01 Added Schematics and updated title
2025-04-01 Updated video
2025-05-05 Updated PCB
2025-05-05 ATMEGA32U4 option
2025-05-07 Working code for the prototype board
2025-05-07 Updated schematic for Pro Micro
2025-10-13 improvements for first prototype
    added 3 mpr121 support, haven't figured out crashing issue
2025-10-15 STM32F411CEU6 Implementation
    ported the code into stm32 platform for more robustness on the i2c bus.
2026-02-11 fixed missing pull up on multiplexer
2026-02-11 first revision
2026-03-02 Cleaned the branch with only relevant files
    It was a mess, trying to clean it up and manage the git properly
2026-03-02 Revision 2 of the PCB
    Updated to using stm32f4 and a more modular design
2026-03-27 Updated side pads with power and ground
2026-06-11 gpy2 sensor instead of tof
